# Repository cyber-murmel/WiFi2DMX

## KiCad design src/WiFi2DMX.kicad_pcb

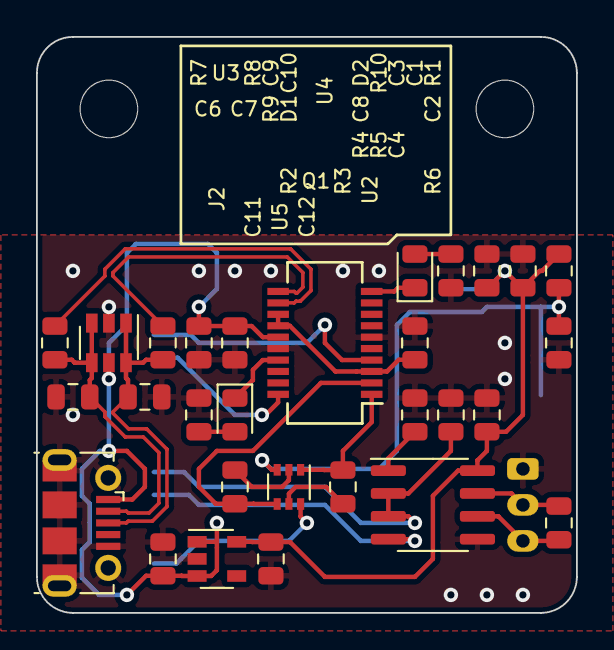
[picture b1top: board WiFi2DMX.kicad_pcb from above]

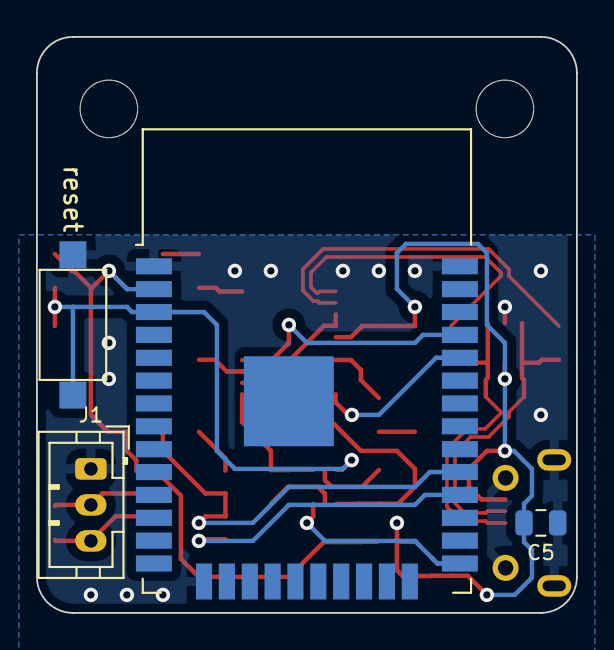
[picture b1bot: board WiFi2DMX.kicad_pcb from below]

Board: 2 copper layers, 30.0 x 32.0 mm, 35 parts (4 on the bottom side), 25 nets.

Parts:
C1, C11, C12: 1u; C_0805_2012Metric
C2, C3: 100n; C_0805_2012Metric
C4: C; C_0805_2012Metric
C5: 10nF; C_0805_2012Metric
C6, C7: 47p; C_0805_2012Metric
C8, C9: 100nF; C_0805_2012Metric
C10: 4.7u; C_0805_2012Metric
D1: red; LED_0805_2012Metric
D2: teal; LED_0805_2012Metric
H1, H2: MountingHole; MountingHole_3.2mm_M3
J1: XLR3; JST_PH_B3B-PH-K_1x03_P2.00mm_Vertical
J2: USB_B_Micro; USB_Micro-B_Molex-105017-0001
Q1: FDG1024NZ; SOT-363_SC-70-6
R1, R2, R3: 10k; R_0805_2012Metric
R4, R5, R9, R10: R; R_0805_2012Metric
R6: 120; R_0805_2012Metric
R7, R8: 27; R_0805_2012Metric
SW1: reset; SW_SPST_CK_RS282G05A3
U1: ESP32-WROOM-32
U2: MAX3072E; SOIC-8_3.9x4.9mm_P1.27mm
U3: USBLC6-2SC6; SOT-23-6
U4: FT231XS; SSOP-20_3.9x8.7mm_P0.635mm
U5: AP2112K-3.3; SOT-23-5

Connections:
+3V3: C1.1, C3.2, C4.1, C12.2, R1.2, U1.2, U2.8, U5.5
/485+: J1.3, R6.2, U2.6
/485-: J1.2, R6.1, U2.7
/DE: R5.1, U1.29, U2.2, U2.3
/FT231XS/D+: C7.1, J2.3, R8.2, U3.1, U3.6
/FT231XS/D-: C6.1, J2.2, R7.2, U3.3, U3.4
/FT231XS/USBD_N: R7.1, U4.12
/FT231XS/USBD_P: R8.1, U4.11
/FT231XS/~RXLED~: D1.1, U4.17
/FT231XS/~TXLED~: D2.1, U4.10
/MODE: Q1.6, U1.25
/U0RXD0: U1.34, U4.20
/U0TXD0: U1.35, U4.4
/U2TXD: U1.28, U2.4
/~DTR~: Q1.1, R3.2, U4.1
/~RESET~: C2.2, Q1.3, R1.1, SW1.2, U1.3
/~RTS~: Q1.4, R2.2, U4.2
GND: C1.2, C2.1, C3.1, C4.2, C5.1, C6.2, C7.2, C8.2, C9.2, C10.2, C11.1, C12.1, J1.1, J2.5, J2.6, R4.2, R5.2, R9.1, R10.1, SW1.1, U1.1, U1.15, U1.38, U2.5, U3.2, U4.6, U4.16, U5.2
unnamed: C8.1, U4.3, U4.13, U4.14
unnamed: D1.2, R9.2
unnamed: D2.2, R10.2
unnamed: Q1.2, R2.1
unnamed: Q1.5, R3.1
unnamed: R4.1, U2.1
VBUS: C5.2, C9.1, C10.1, C11.2, J2.1, U3.5, U4.15, U5.1, U5.3
